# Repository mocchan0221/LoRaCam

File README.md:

# LoRaCam
AI camera via LoRa on Raspberry Pi

Raspberry Pi + カメラで YOLOv8n (TFLite) による人数カウントを行い、結果を CSV に記録しつつ LoRaWAN で送信するデバイス。

## 動作環境
- Raspberry Pi Zero 2 W / Raspberry Pi OS Bookworm (Python 3.11)
- Camera Module 3 (imx708)
- LoRa モジュール A660-900T22 (UART `/dev/ttyS0`, 9600bps) — AS923-1 (日本), OTAA, Class A

## ディレクトリ構成
| パス | 内容 |
| --- | --- |
| `main.py` | エントリポイント (設定読込 → Wi-Fi/ホスト名設定 → LoRa Join → 撮影・検出・送信ループ) |
| `app/` | 各種機能 (カメラ, 検出器, ログ, LoRa通信, 設定, システム初期化) |
| `models/` | YOLO モデル置き場 (git管理外) |
| `data/images`, `data/logs` | 最新の検出画像・CSVログ (git管理外) |
| `services/` | systemd サービス定義 |
| `scripts/dev_update.sh` | 開発機用ワンクリック更新スクリプト |
| `LoRaTest.py`, `SystemTest.py` | LoRa 通信 / システム設定の単体テスト |
| `pcb/` | 基板データ (KiCad) |

## セットアップ (開発機)
サービス定義と更新スクリプトはユーザー `jkkb`、パス `/home/jkkb/LoRaCam` 前提。

1. `sudo raspi-config` → Interface Options → Serial Port で「Login shell: No」「Serial port hardware: Yes」にして再起動
2. リポジトリを取得して仮想環境を作成
   ```bash
   cd ~ && git clone https://github.com/mocchan0221/LoRaCam.git && cd LoRaCam
   sudo apt install -y python3-picamera2 python3-opencv
   python3 -m venv --system-site-packages .venv   # apt の picamera2 を venv から使うため
   .venv/bin/pip install -r requirements.txt
   ```
   - tflite-runtime は numpy 2.x では動かないため `numpy<2` (requirements では 1.26.4) を使う
   - シリアル通信は `pyserial`。`serial` パッケージを入れると `module 'serial' has no attribute 'Serial'` になる
3. モデルを用意 (PC 側で変換して `models/` にコピー)
   ```bash
   pip install ultralytics
   yolo export model=yolov8n.pt format=tflite int8
   # → yolov8n_saved_model/yolov8n_full_integer_quant.tflite を models/ へ
   ```
4. 設定ファイルを配置: `config_template.json` を `/boot/firmware/config.json` にコピーして編集 (下記)
5. サービス登録
   ```bash
   sudo cp services/*.service /etc/systemd/system/
   sudo systemctl daemon-reload
   sudo systemctl enable --now LoRaCam.service WebMonitor.service
   ```

## 設定 (`/boot/firmware/config.json`)
| キー | 内容 |
| --- | --- |
| `LoRa.DEVEUI` / `APPEUI` / `APPKEY` | OTAA 用のキー |
| `LoRa.IsJoined` | 1 なら起動時の Join をスキップ |
| `Camera.Focus` | マニュアルフォーカス値 (LensPosition, 0.0 = 無限遠) |
| `Network.wifi_enabled` | 0: Wi-Fi OFF / 1: Wi-Fi ON (`SSID`, `PASSWORD` に接続) |
| `Network.HostName` | ホスト名 (`.local` は付けない。例: `jkkb1` → `jkkb1.local` でアクセス) |
| `Network.IsLatest` | 0 にすると次回起動時に Wi-Fi・ホスト名を適用し、1 に書き換えて再起動 |
| `Detection.Interval` | 検出・送信の間隔 [秒] |
| `Detection.CONF_THRESHOLD` | 検出の信頼度しきい値 |

## 動作確認
```bash
journalctl -u LoRaCam.service -f          # 本体のログ
sudo .venv/bin/python LoRaTest.py         # 対話式 LoRa テスト (join / send / recv / at)
sudo .venv/bin/python SystemTest.py       # Wi-Fi・ホスト名設定のテスト (IsLatest=0 のとき再起動する)
```
LoRaTest を使う前に `sudo systemctl stop LoRaCam.service` でシリアルポートを空けておく。

出力:
- `data/logs/logPerson.csv` (人数), `logAll.csv` (全クラス), `logLoRa.csv` (送受信履歴)
- `data/images/latest_result.jpg` (最新の検出画像)
- WebMonitor により `http://<ホスト名>.local:8000/data/` から閲覧可能
- LoRa 送信ペイロード: `"YYYY-mm-dd HH:MM:SS <人数>"` の ASCII 文字列

### ステータスLED
| 緑 (GPIO17) | 赤 (GPIO27) | 状態 |
| --- | --- | --- |
| 点滅 | 消灯 | 初期化中 (設定読込・カメラ・LoRa Join) |
| 点灯 | 消灯 | 正常動作中 |
| 消灯 | 点灯 | 異常終了 (エラー終了・クラッシュ・120秒応答なし)。10秒後に自動再起動 |
| 点滅 | 点灯 | 異常終了後の再起動中。正常動作に入ると赤は消える |
| 消灯 | 消灯 | サービス停止中 |

赤点灯の原因は `journalctl -u LoRaCam.service` と `/run/loracam-error` で確認できる。

## 開発フロー
PC で編集して push → 開発機で `bash scripts/dev_update.sh` (sudo は付けない)。pull・サービス更新・再起動を一括で行い、pip は requirements.txt が変わったときだけ実行 (`--force-pip` で強制)。

## デバイスの複製
1. 開発機の SD カードを Win32 Disk Imager でイメージ化 (必要なら WSL2/Linux の pishrink で圧縮)
2. Raspberry Pi Imager 等で新しい SD カードに書き込み
3. PC から bootfs パーティションの `config.json` を個体ごとに編集 (キー、ホスト名など。`IsLatest: 0`, `IsJoined: 0`)
4. 電源投入で初回にネットワーク設定を適用して再起動し、以降は自動で動作開始

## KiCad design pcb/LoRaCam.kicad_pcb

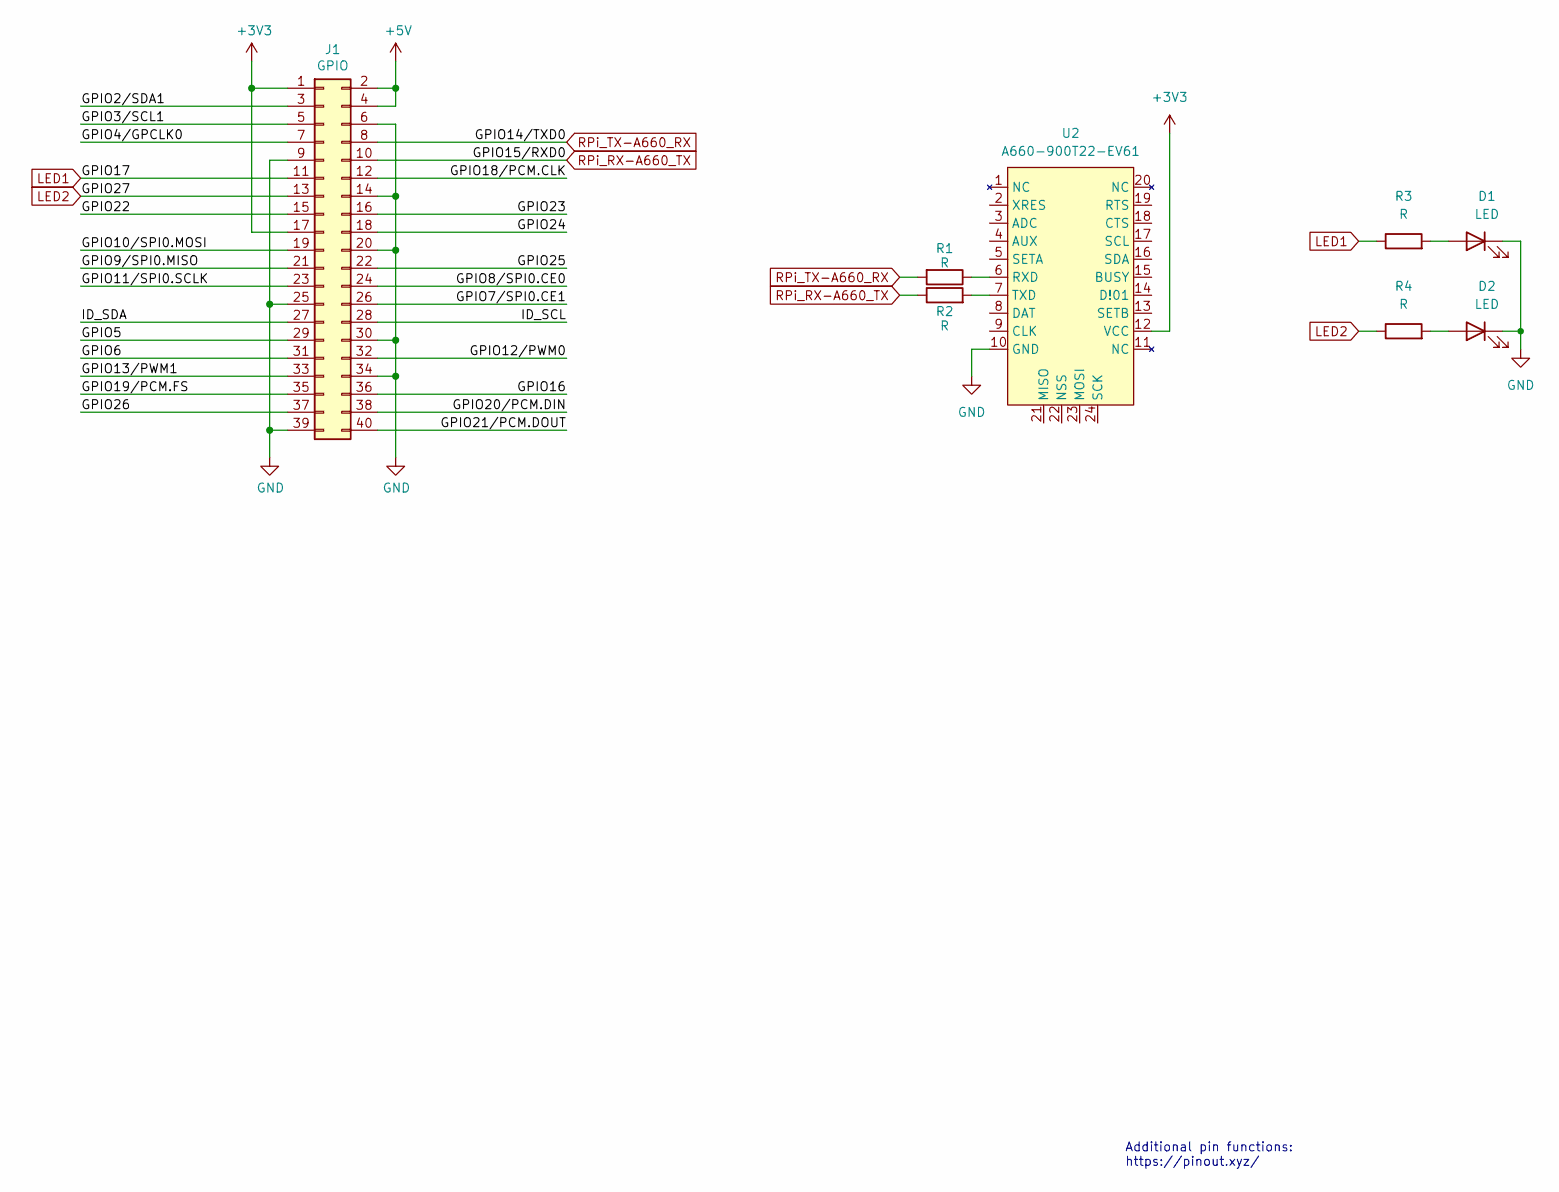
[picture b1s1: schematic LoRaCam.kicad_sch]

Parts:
D1, D2: LED; LED_D5.0mm
J1: GPIO; PinSocket_2x20_P2.54mm_Vertical
R1, R2, R3, R4: R; R_Axial_DIN0207_L6.3mm_D2.5mm_P7.62mm_Horizontal
U2: A660-900T22-EV61

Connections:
+3V3: J1.1, J1.17, U2.12 (VCC)
+5V: J1.2, J1.4
/GPIO2/SDA1: J1.3
/GPIO3/SCL1: J1.5
/GPIO4/GPCLK0: J1.7
/GPIO5: J1.29
/GPIO6: J1.31
/GPIO7/SPI0.CE1: J1.26
/GPIO8/SPI0.CE0: J1.24
/GPIO9/SPI0.MISO: J1.21
/GPIO10/SPI0.MOSI: J1.19
/GPIO11/SPI0.SCLK: J1.23
/GPIO12/PWM0: J1.32
/GPIO13/PWM1: J1.33
/GPIO16: J1.36
/GPIO18/PCM.CLK: J1.12
/GPIO19/PCM.FS: J1.35
/GPIO20/PCM.DIN: J1.38
/GPIO21/PCM.DOUT: J1.40
/GPIO22: J1.15
/GPIO23: J1.16
/GPIO24: J1.18
/GPIO25: J1.22
/GPIO26: J1.37
/ID_SCL: J1.28
/ID_SDA: J1.27
GND: D1.1 (K), D2.1 (K), J1.6, J1.9, J1.14, J1.20, J1.25, J1.30, J1.34, J1.39, U2.10 (GND)
LED1: J1.11, R3.1
LED2: J1.13, R4.1
unnamed: D1.2 (A), R3.2
unnamed: D2.2 (A), R4.2
unnamed: R1.1, U2.6 (RXD)
unnamed: R2.2, U2.7 (TXD)
RPi_RX-A660_TX: J1.10, R2.1
RPi_TX-A660_RX: J1.8, R1.2

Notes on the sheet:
Additional pin functions: https://pinout.xyz/

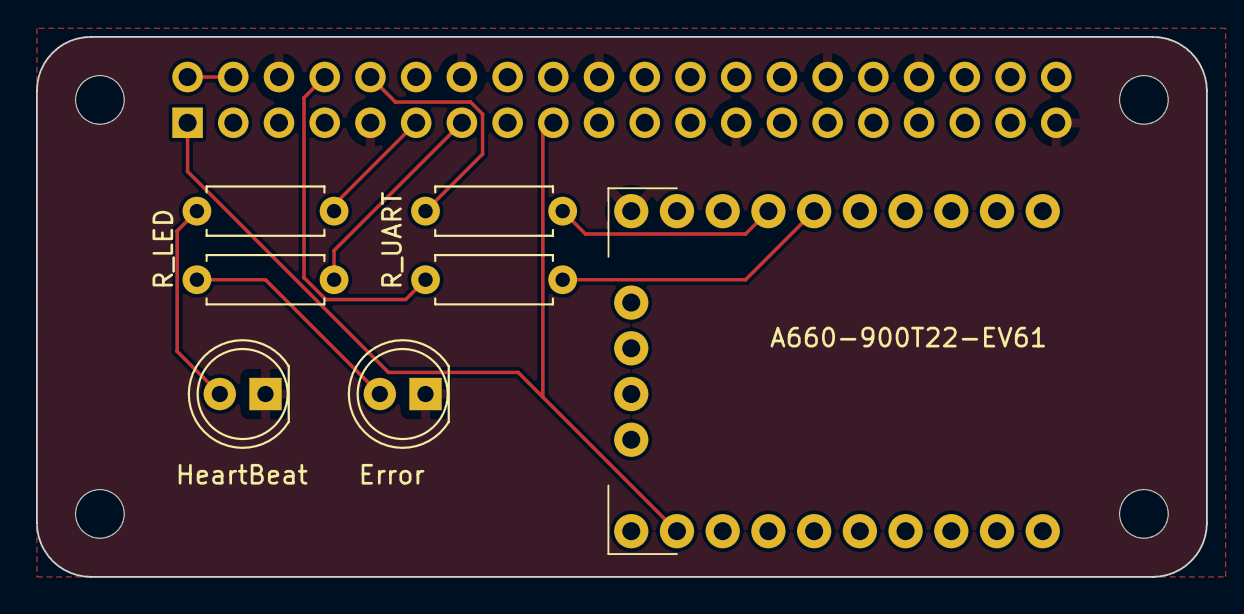
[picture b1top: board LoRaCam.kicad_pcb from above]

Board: 2 copper layers, 65.0 x 30.0 mm, 12 parts (1 on the bottom side), 11 nets.

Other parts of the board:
MH1, MH2, MH3, MH4: MountingHole_2.7mm_M2.5

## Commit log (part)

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2026-01-14 add minimum functions
2026-01-14 add data, models dir
2026-01-14 remove PyQt5 from requirements
2026-01-14 remove python-apt
2026-01-14 modify
2026-01-14 load_config
2026-01-14 initをinit
2026-01-14 add config loading log
2026-01-14 modify service
2026-01-14 Modify update script
2026-01-14 typo
2026-01-15 add LoRa function and test
2026-01-15 add pyserial to req
2026-01-15 add lora function to main
2026-01-15 time
2026-01-15 add img dir
2026-01-15 mod dir
2026-01-16 add pcb and modify gitignore
2026-01-22 change region
2026-01-22 set camera RGB
2026-01-22 change status check
2026-01-22 change join process
2026-01-22 enable join skip
2026-01-22 add date data
2026-01-22 change some configs
2026-01-22 add requirements
2026-01-22 add system config
2026-01-24 modify LoRaTest
2026-01-24 modify system init and add test
2026-01-24 add lora log
2026-01-24 add lora check
